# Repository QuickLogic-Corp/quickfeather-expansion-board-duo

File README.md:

# quickfeather-expansion-board-duo

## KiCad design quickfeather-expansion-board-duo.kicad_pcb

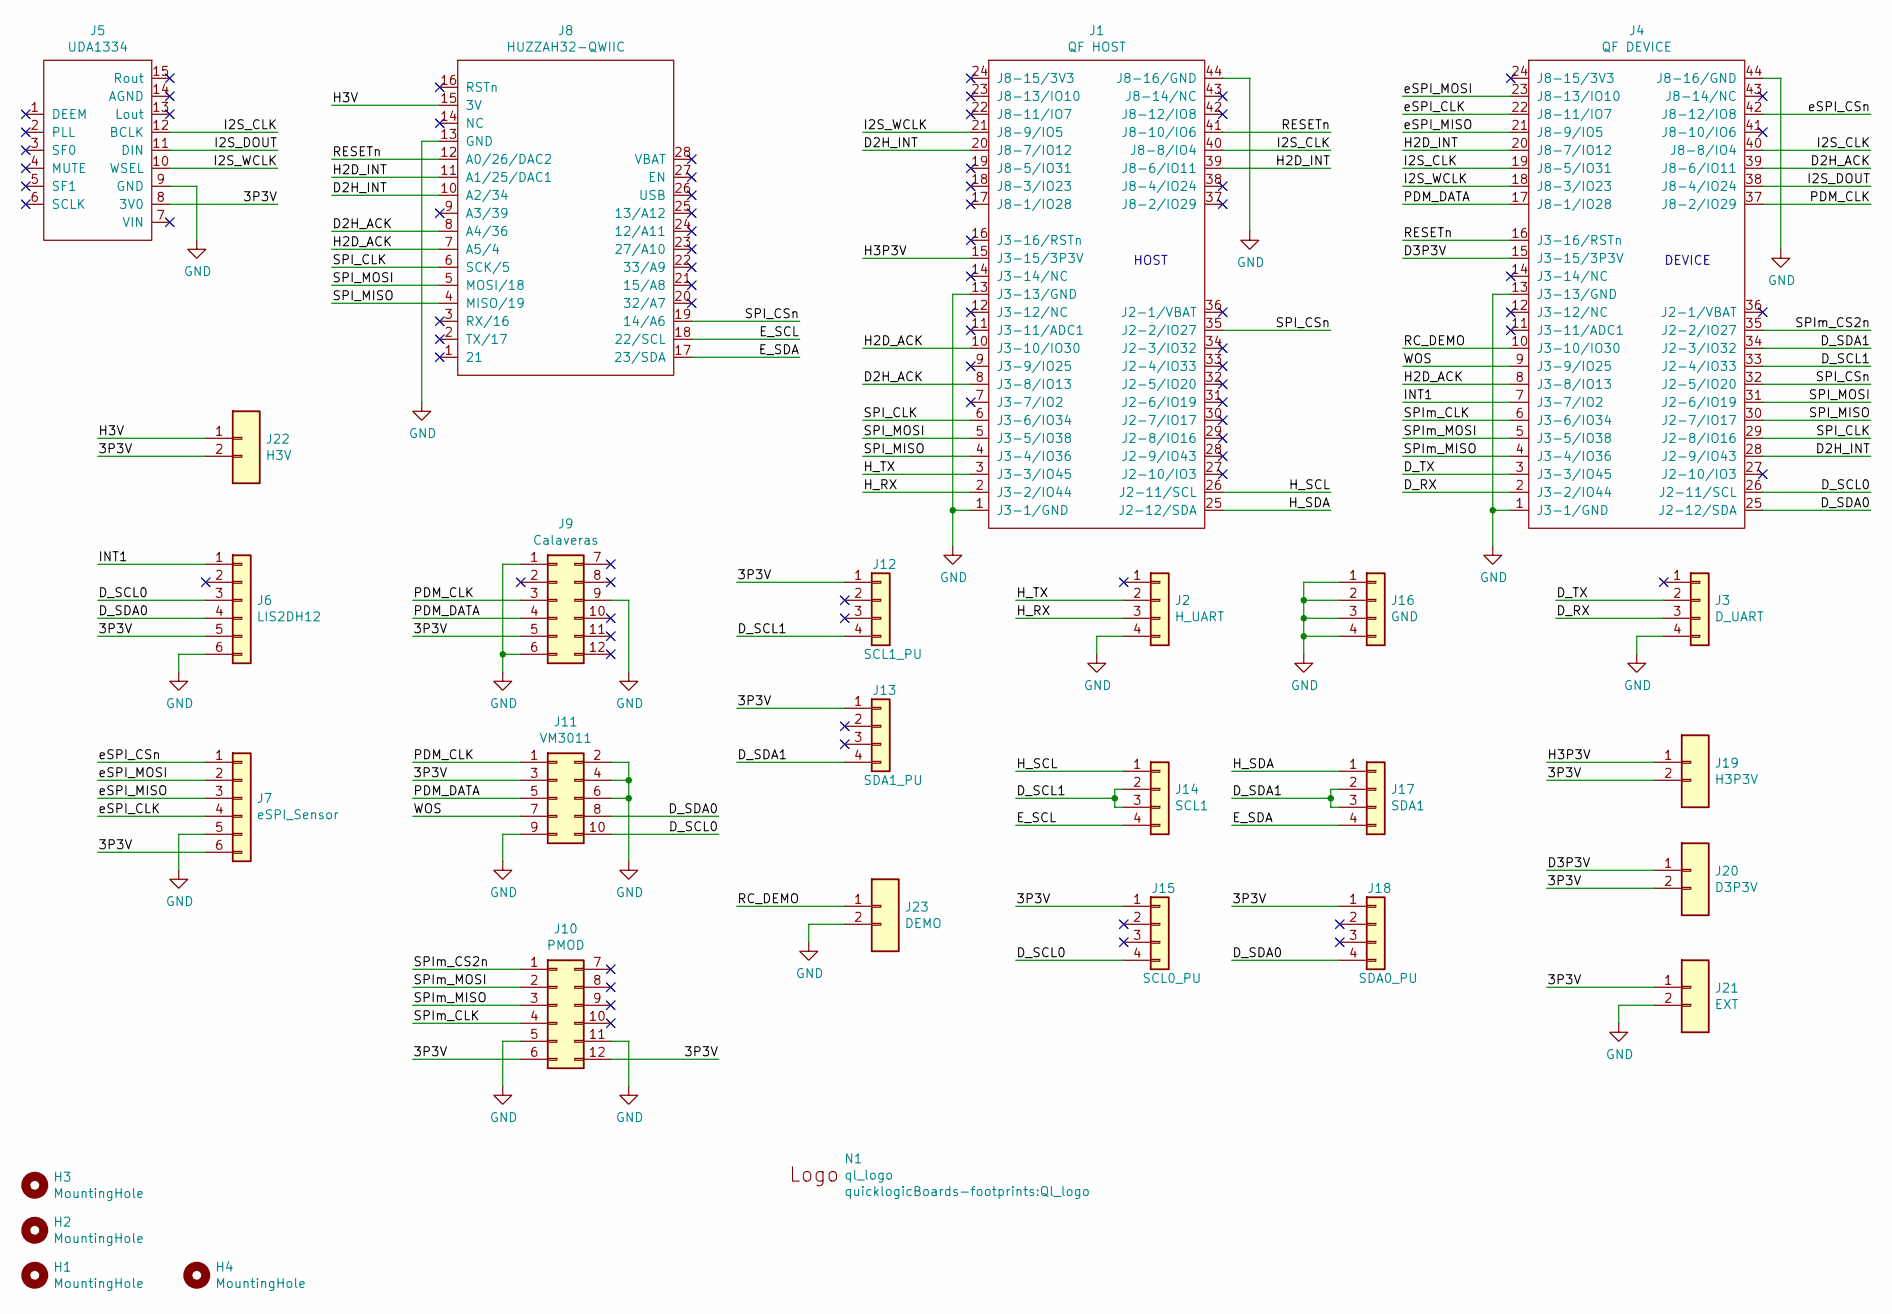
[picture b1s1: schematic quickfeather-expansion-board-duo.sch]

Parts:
H1, H2, H3, H4: MountingHole; MPAD
J1: QF HOST; quickfeather
J2: H_UART; 1x4_Conn
J3: D_UART; 1x4_Conn
J4: QF DEVICE; quickfeather
J5: UDA1334; uda1334
J6: LIS2DH12; 1x6_Conn
J7: eSPI_Sensor; 1x6_pinhead
J8: HUZZAH32-QWIIC; huzzah32
J9: Calaveras; 2x6_Conn
J10: PMOD; 2x6_Conn
J11: VM3011; 2x5_Conn
J12: SCL1_PU; 1x4_Conn
J13: SDA1_PU; 1x4_Conn
J14: SCL1; 1x4_Conn
J15: SCL0_PU; 1x4_Conn
J16: GND; 1x4_Conn
J17: SDA1; 1x4_Conn
J18: SDA0_PU; 1x4_Conn
J19: H3P3V; 1x2_Conn
J20: D3P3V; 1x2_Conn
J21: EXT; 1x2_Conn
J22: H3V; 1x2_Conn
J23: DEMO; 1x2_Conn
N1: ql_logo; Ql_logo

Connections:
/3P3V: J5.8 (3V0), J6.5, J7.6, J9.5, J10.6, J10.12, J11.3, J12.1, J13.1, J15.1, J18.1, J19.2, J20.2, J21.1, J22.2
/D2H_ACK: J1.8 (J3-8/IO13), J4.39 (J8-6/IO11), J8.8 (A4/36)
/D2H_INT: J1.20 (J8-7/IO12), J4.28 (J2-9/IO43), J8.10 (A2/34)
/D3P3V: J4.15 (J3-15/3P3V), J20.1
/D_RX: J3.3, J4.2 (J3-2/IO44)
/D_SCL0: J4.26 (J2-11/SCL), J6.3, J11.10, J15.4
/D_SCL1: J4.33 (J2-4/IO33), J12.4, J14.2, J14.3
/D_SDA0: J4.25 (J2-12/SDA), J6.4, J11.8, J18.4
/D_SDA1: J4.34 (J2-3/IO32), J13.4, J17.2, J17.3
/D_TX: J3.2, J4.3 (J3-3/IO45)
/E_SCL: J8.18 (22/SCL), J14.4
/E_SDA: J8.17 (23/SDA), J17.4
/H2D_ACK: J1.10 (J3-10/IO30), J4.8 (J3-8/IO13), J8.7 (A5/4)
/H2D_INT: J1.39 (J8-6/IO11), J4.20 (J8-7/IO12), J8.11 (A1/25/DAC1)
/H3P3V: J1.15 (J3-15/3P3V), J19.1
/H3V: J8.15 (3V), J22.1
/H_RX: J1.2 (J3-2/IO44), J2.3
/H_SCL: J1.26 (J2-11/SCL), J14.1
/H_SDA: J1.25 (J2-12/SDA), J17.1
/H_TX: J1.3 (J3-3/IO45), J2.2
/I2S_CLK: J1.40 (J8-8/IO4), J4.19 (J8-5/IO31), J4.40 (J8-8/IO4), J5.12 (BCLK)
/I2S_DOUT: J4.38 (J8-4/IO24), J5.11 (DIN)
/I2S_WCLK: J1.21 (J8-9/IO5), J4.18 (J8-3/IO23), J5.10 (WSEL)
/INT1: J4.7 (J3-7/IO2), J6.1
/PDM_CLK: J4.37 (J8-2/IO29), J9.3, J11.1
/PDM_DATA: J4.17 (J8-1/IO28), J9.4, J11.5
/RC_DEMO: J4.10 (J3-10/IO30), J23.1
/RESETn: J1.41 (J8-10/IO6), J4.16 (J3-16/RSTn), J8.12 (A0/26/DAC2)
/SPI_CLK: J1.6 (J3-6/IO34), J4.29 (J2-8/IO16), J8.6 (SCK/5)
/SPI_CSn: J1.35 (J2-2/IO27), J4.32 (J2-5/IO20), J8.19 (14/A6)
/SPI_MISO: J1.4 (J3-4/IO36), J4.30 (J2-7/IO17), J8.4 (MISO/19)
/SPI_MOSI: J1.5 (J3-5/IO38), J4.31 (J2-6/IO19), J8.5 (MOSI/18)
/SPIm_CLK: J4.6 (J3-6/IO34), J10.4
/SPIm_CS2n: J4.35 (J2-2/IO27), J10.1
/SPIm_MISO: J4.4 (J3-4/IO36), J10.3
/SPIm_MOSI: J4.5 (J3-5/IO38), J10.2
/WOS: J4.9 (J3-9/IO25), J11.7
/eSPI_CLK: J4.22 (J8-11/IO7), J7.4
/eSPI_CSn: J4.42 (J8-12/IO8), J7.1
/eSPI_MISO: J4.21 (J8-9/IO5), J7.3
/eSPI_MOSI: J4.23 (J8-13/IO10), J7.2
GND: J1.1 (J3-1/GND), J1.13 (J3-13/GND), J1.44 (J8-16/GND), J2.4, J3.4, J4.1 (J3-1/GND), J4.13 (J3-13/GND), J4.44 (J8-16/GND), J5.9 (GND), J6.6, J7.5, J8.13 (GND), J9.1, J9.6, J9.9, J10.5, J10.11, J11.2, J11.4, J11.6, J11.9, J16.1, J16.2, J16.3, J16.4, J21.2, J23.2

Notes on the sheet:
HOST
DEVICE

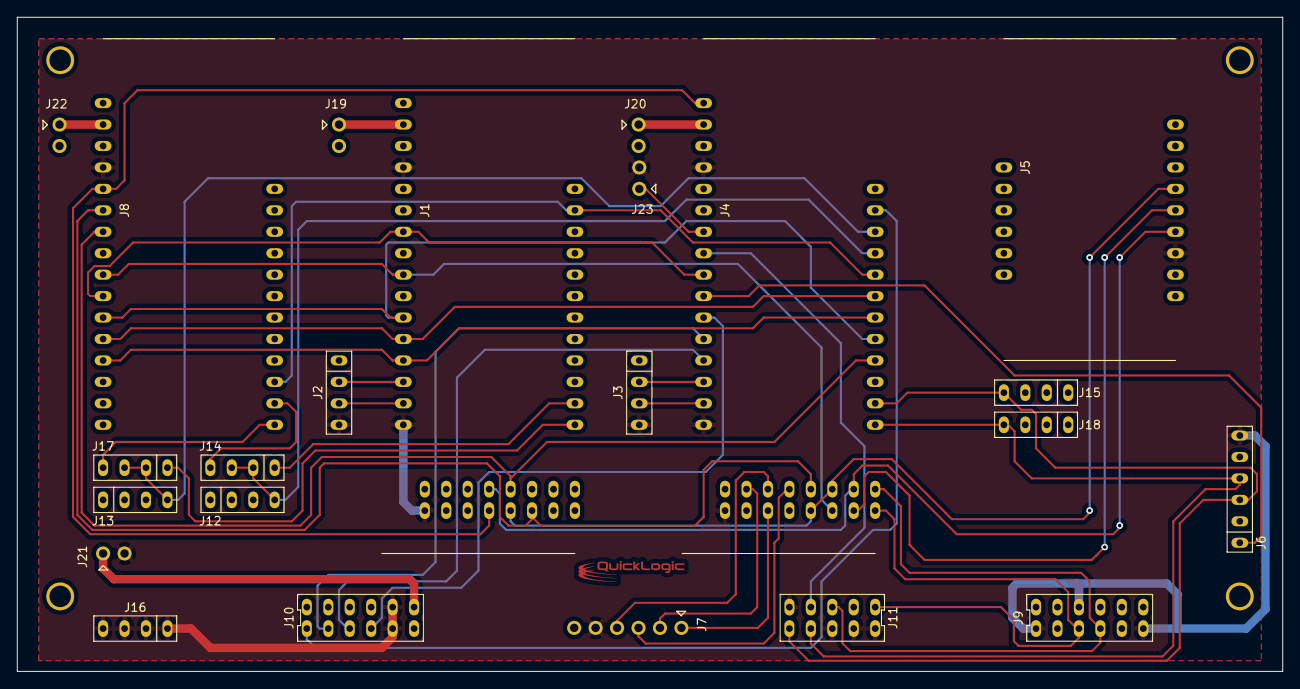
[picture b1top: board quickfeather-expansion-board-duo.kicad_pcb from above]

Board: 2 copper layers, 149.9 x 77.5 mm, 28 parts (0 on the bottom side), 42 nets.

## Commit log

2020-11-02 First draft of schematic and mock layout
2020-11-10 1st Rev of schematic Part Placement - partial
2020-11-10 Added target use cases
2020-11-11 Submit: 1. Latest layout 2. generated schematic 3. Gerber files 4. Updated layout library
